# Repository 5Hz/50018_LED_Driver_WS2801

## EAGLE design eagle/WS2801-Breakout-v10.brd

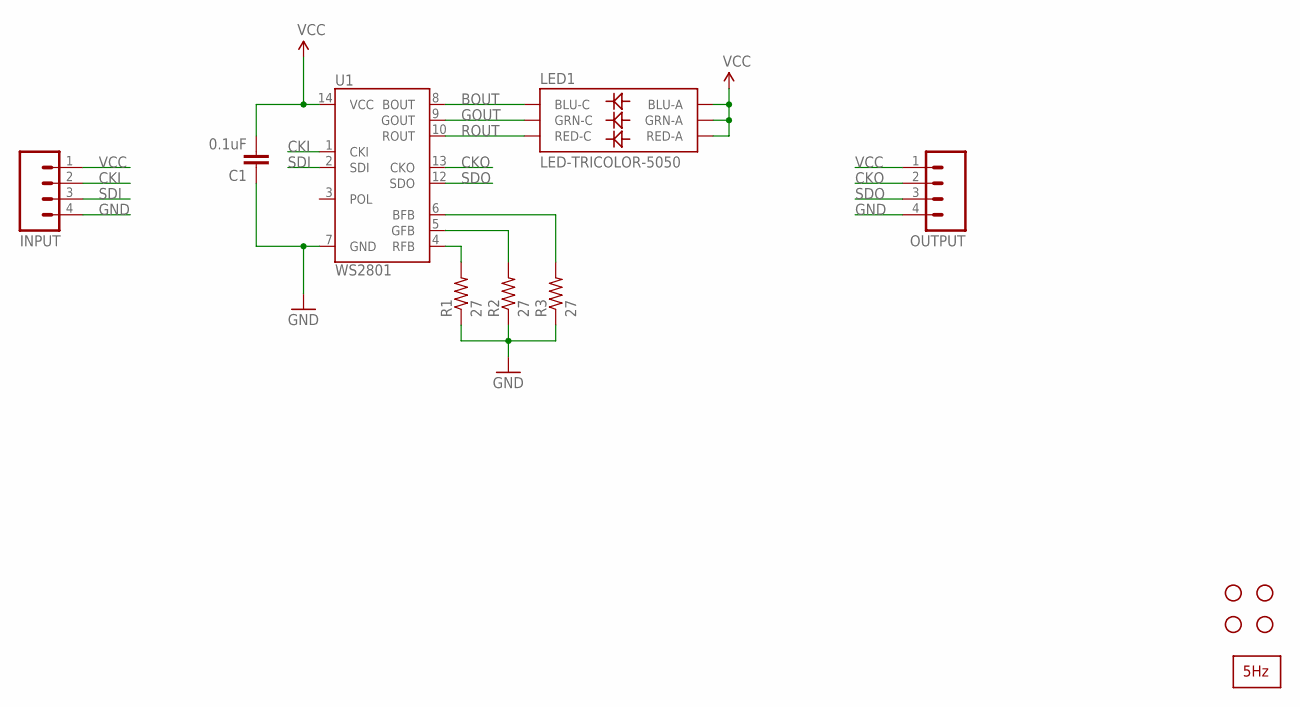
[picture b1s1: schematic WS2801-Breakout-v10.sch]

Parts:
C1: 0.1uF; 0402-CAP
INPUT: M04PTH; 1X04
JP1, JP2, JP4, JP5: STAND-OFF
LED1: LED-TRICOLOR-5050
OUTPUT: M04PTH; 1X04
R1, R2, R3: 27; 0402-RES
U1: WS2801; SOP-14
U$1: LOGO2_SILKC5MM; CIRCULO2_5MM

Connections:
BFB: R3.2, U1.6 (BFB)
BOUT: LED1.4 (BLU-C), U1.8 (BOUT)
CKI: INPUT.2, U1.1 (CKI)
CKO: OUTPUT.2, U1.13 (CKO)
GFB: R2.2, U1.5 (GFB)
GND: C1.1, INPUT.4, OUTPUT.4, R1.1, R2.1, R3.1, U1.7 (GND)
GOUT: LED1.6 (GRN-C), U1.9 (GOUT)
RFB: R1.2, U1.4 (RFB)
ROUT: LED1.5 (RED-C), U1.10 (ROUT)
SDI: INPUT.3, U1.2 (SDI)
SDO: OUTPUT.3, U1.12 (SDO)
VCC: C1.2, INPUT.1, LED1.1 (GRN-A), LED1.2 (RED-A), LED1.3 (BLU-A), OUTPUT.1, U1.14 (VCC)

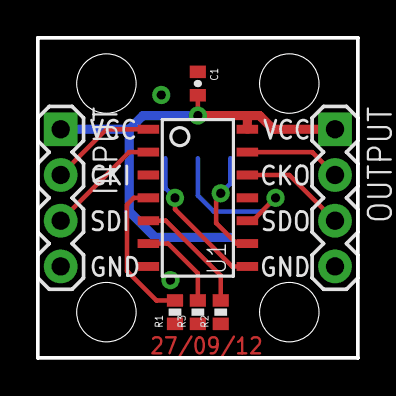
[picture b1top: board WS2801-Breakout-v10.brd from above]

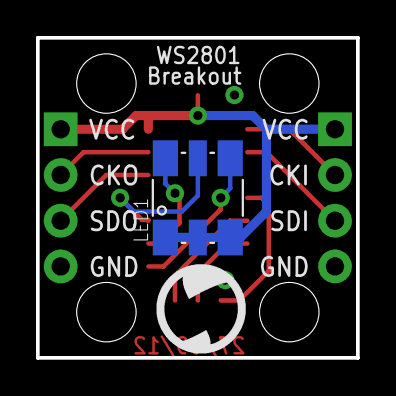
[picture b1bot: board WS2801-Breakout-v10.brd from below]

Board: 2 copper layers, 17.8 x 17.8 mm, 13 parts (2 on the bottom side), 12 nets.

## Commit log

2014-01-10 creación
